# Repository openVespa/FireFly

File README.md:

# FireFly
The digital ignition controller, called the FireFly Mini, uses the stock Variable Reluctor (VR) pickup and is the typical retard only system. Also includes (2) K-type thermocouple inputs for Exhaust Gas Temperature (EGT) and Cylinder Head Temperature (CHT) monitoring. The goal is to provide a programmable ignition controller that dynamically adjusts based on EGT and CHT values.  A Windows program allows you to customize ignition curves over USB; log RPM, CHT, and EGT values; and flash the firmware. You can save maps, read the map that is loaded,etc. I've also created an basic android app that displays the RPM, CHT, and EGT values. In addition, the FF mini simulates the popular OBDII ELM327 interface. This allows my old Vespa to have an "OBD II ecu", allowing you to take advantage of the many ELM327 based apps available. My personal favorite is the Torque app.

The GUI was developed using Microsoft Visual C# 2010 and relies heavily on the Generic HID program and contains portions of the WFF GenericHID Communication Library which is (c)2011 Simon Inns - http://www.waitingforfriday.com 

The Eagle schematics and board files are provided, along with the BOM, and the Gerbers. The circuit card was designed to fit into a Polycase LP-11F enclosure.  The design uses an atmega16u2 and the source code was developed in Atmel Studio 6.1.  The USB stack is based on the LUFA USB Library.

http://www.fourwalledcubicle.com/LUFA.php

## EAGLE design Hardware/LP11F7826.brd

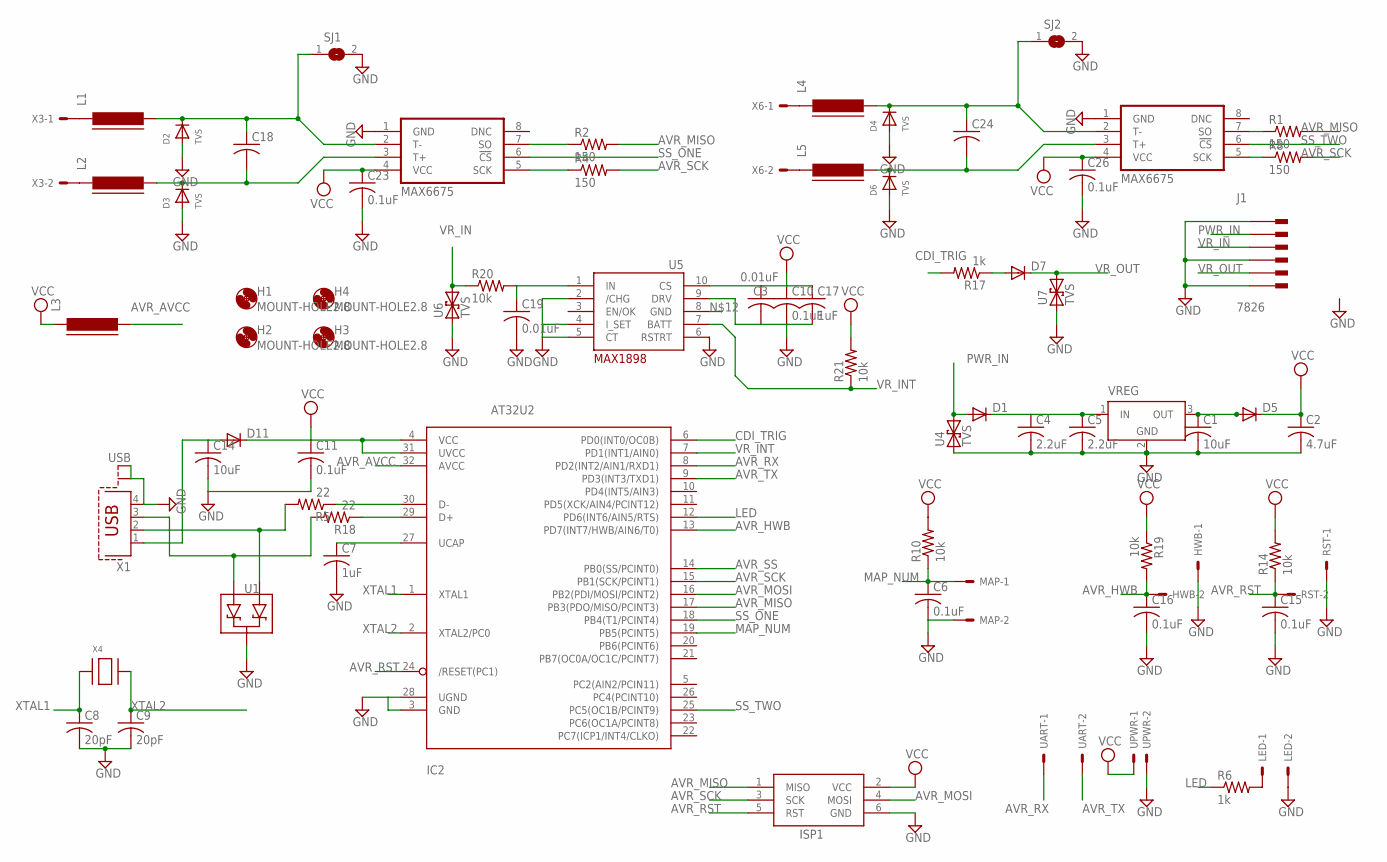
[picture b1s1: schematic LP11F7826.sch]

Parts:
C1: 10uF; C1206
C2: 4.7uF; C1210
C3, C19: 0.01uF; C0805
C4: 2.2uF; C1206
C5: 2.2uF; C1210
C6, C10, C11, C15, C16, C23, C26: 0.1uF; C0805
C7, C17: 1uF; C0805
C8, C9: 20pF; C0805
C14: 10uF; C0805
C18, C24: C-USC0805; C0805
D1, D5, D7, D11: CGRM4001-G; SOD-123_MINI-SMA
D2, D3, D4, D6: TVS; SOD-323F
H1, H2, H3, H4: MOUNT-HOLE2.8; 2,8
HWB: 87758-0216; MPN 87758-0216
IC1, IC3: MAX6675; SO-8
IC2: AT32U2; TQFP32-08
ISP1: AVRISP-6; AVRISP
J1: 7826; 7806HEADER
L1, L2, L3, L4, L5: FERRITE-0805; FB805
LED: 87758-0216; MPN 87758-0216
MAP: 87758-0216
R1, R2, R4, R8: 150; R0805
R5, R18: 22; R0805
R6, R17: 1k; R0805
R10, R14, R19, R20, R21: 10k; R0805
RST: 87758-0216; MPN 87758-0216
SJ1, SJ2: SJ
U1: MMBZ27VCLT1; SOT23-3
U4, U6, U7: TVS; SMA-DIODE
U5: MAX9924; UMAX10
UART: 87758-0216; MPN 87758-0216
UPWR: 87758-0216; MPN 87758-0216
VREG: LT1963EST-3.3; SOT223
X1: USB; PN61729-S
X3, X6: 22-23-2021; MPN 22-23-2021
X4: XTALNX5032; NX5032

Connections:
AVR_AVCC: IC2.32 (AVCC), L3.2
AVR_HWB: C16.1, HWB.2, IC2.13 (PD7(INT7/HWB/AIN6/T0)), R19.2
AVR_MISO: IC2.17 (PB3(PDO/MISO/PCINT3)), ISP1.1 (MISO), R1.2, R2.2
AVR_MOSI: IC2.16 (PB2(PDI/MOSI/PCINT2)), ISP1.4 (MOSI)
AVR_RST: C15.1, IC2.24 (/RESET(PC1)), ISP1.5 (RST), R14.1, RST.2
AVR_RX: IC2.8 (PD2(INT2/AIN1/RXD1)), UART.1
AVR_SCK: IC2.15 (PB1(SCK/PCINT1)), ISP1.3 (SCK), R4.2, R8.2
AVR_SS: IC2.14 (PB0(SS/PCINT0))
AVR_TX: IC2.9 (PD3(INT3/TXD1)), UART.2
CDI_TRIG: IC2.6 (PD0(INT0/OC0B)), R17.2
GND: C1.2, C2.2, C3.2, C4.2, C5.2, C6.2, C7.2, C8.2, C9.2, C10.2, C11.2, C14.2, C15.2, C16.2, C17.2, C19.2, C23.2, C26.2, D2.A, D3.A, D4.A, D6.A, HWB.1, IC1.1 (GND), IC2.3 (GND), IC2.28 (UGND), IC3.1 (GND), ISP1.6 (GND), J1.A1 (1), J1.A2 (1), J1.A5 (3), J1.A6 (3), J1.A11 (6), J1.A12 (6), LED.2, MAP.2, RST.1, SJ1.2, SJ2.2, U1.3 (C), U4.A (1), U5.2 (/CHG), U5.4 (I_SET), U5.5 (CT), U5.6 (RSTRT), U5.9 (DRV), U6.A (1), U7.A (1), UPWR.2, VREG.2 (GND), VREG.4 (GND), X1.4, X1.S1, X1.S2
LED: IC2.12 (PD6(INT6/AIN5/RTS)), R6.1
MAP_NUM: C6.1, IC2.19 (PB5(PCINT5)), MAP.1, R10.1
unnamed: C14.1, D11.A, X1.1
unnamed: C4.1, C5.1, D1.C, VREG.1 (IN)
unnamed: C18.1, D2.C, IC3.2 (T-), L1.2, SJ1.1
unnamed: C18.2, D3.C, IC3.3 (T+), L2.2
unnamed: C1.1, D5.A, VREG.3 (OUT)
unnamed: LED.1, R6.2
unnamed: C24.1, D4.C, IC1.2 (T-), L4.2, SJ2.1
unnamed: C24.2, D6.C, IC1.3 (T+), L5.2
unnamed: IC1.5 (SCK), R8.1
unnamed: IC2.30 (D-), R5.1
unnamed: L1.1, X3.1
unnamed: L2.1, X3.2
unnamed: IC3.5 (SCK), R4.1
unnamed: IC2.29 (D+), R18.1
unnamed: C7.1, IC2.27 (UCAP)
unnamed: IC3.7 (SO), R2.1
unnamed: IC1.7 (SO), R1.1
unnamed: L4.1, X6.1
unnamed: L5.1, X6.2
unnamed: R5.2, U1.1 (A1), X1.2
unnamed: R18.2, U1.2 (A2), X1.3
unnamed: D7.A, R17.1
unnamed: C19.1, R20.2, U5.1 (IN)
PWR_IN: D1.A, J1.A9 (5), J1.A10 (5), U4.C (2)
SS_ONE: IC2.18 (PB4(T1/PCINT4)), IC3.6 (!CS)
SS_TWO: IC1.6 (!CS), IC2.25 (PC5(OC1B/PCINT9))
VCC: C2.1, C3.1, C10.1, C11.1, C17.1, C23.1, C26.1, D5.C, D11.C, IC1.4 (VCC), IC2.4 (VCC), IC2.31 (UVCC), IC3.4 (VCC), ISP1.2 (VCC), L3.1, R10.2, R14.2, R19.1, R21.2, U5.10 (CS), UPWR.1
VR_IN: J1.A7 (4), J1.A8 (4), R20.1, U6.C (2)
VR_INT: IC2.7 (PD1(INT1/AIN0)), R21.1, U5.7 (BATT)
VR_OUT: D7.C, J1.A3 (2), J1.A4 (2), U7.C (2)
XTAL1: C8.1, IC2.1 (XTAL1), X4.P$1
XTAL2: C9.1, IC2.2 (XTAL2/PC0), X4.P$2

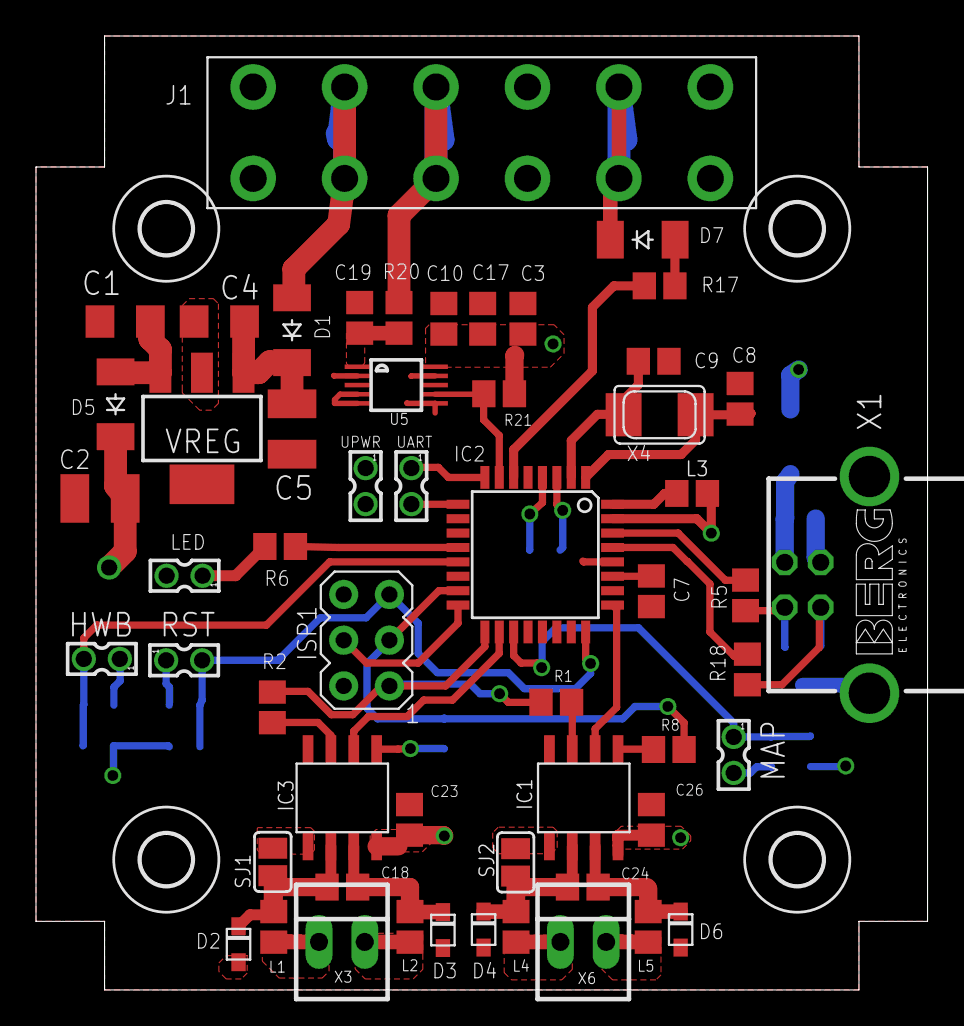
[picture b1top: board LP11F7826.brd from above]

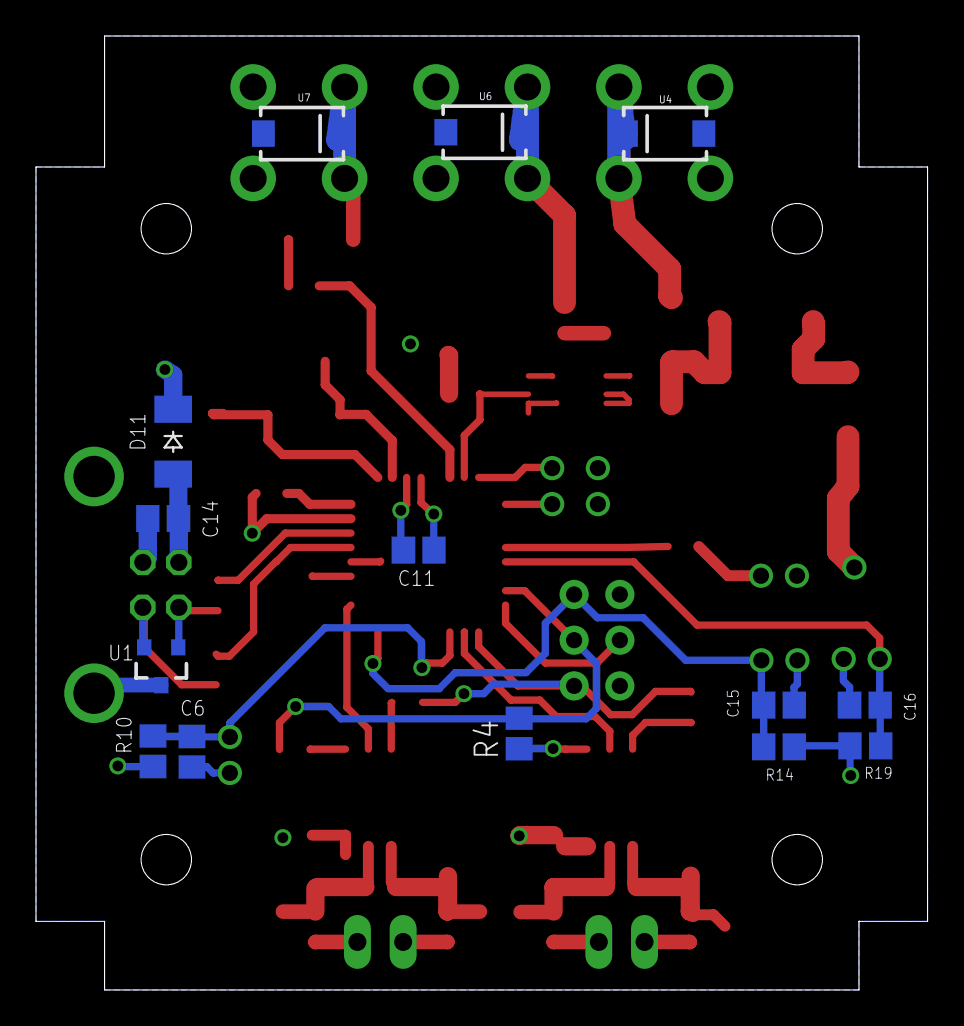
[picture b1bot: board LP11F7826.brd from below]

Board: 2 copper layers, 49.5 x 53.0 mm, 73 parts (14 on the bottom side), 44 nets.

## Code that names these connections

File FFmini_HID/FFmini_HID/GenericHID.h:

/*
             LUFA Library
     Copyright (C) Dean Camera, 2014.

  dean [at] fourwalledcubicle [dot] com
           www.lufa-lib.org
*/

/*
  Copyright 2014  Dean Camera (dean [at] fourwalledcubicle [dot] com)

  Permission to use, copy, modify, distribute, and sell this
  software and its documentation for any purpose is hereby granted
  without fee, provided that the above copyright notice appear in
  all copies and that both that the copyright notice and this
  permission notice and warranty disclaimer appear in supporting
  documentation, and that the name of the author not be used in
  advertising or publicity pertaining to distribution of the
  software without specific, written prior permission.

  The author disclaims all warranties with regard to this
  software, including all implied warranties of merchantability
  and fitness.  In no event shall the author be liable for any
  special, indirect or consequential damages or any damages
  whatsoever resulting from loss of use, data or profits, whether
  in an action of contract, negligence or other tortious action,
  arising out of or in connection with the use or performance of
  this software.
*/

/** \file
 *
 *  Header file for GenericHID.c.
 */

#ifndef _GENERICHID_H_
#define _GENERICHID_H_

	/* Includes: */
		#include <avr/pgmspace.h>
		#include <avr/io.h>
		#include <avr/wdt.h>
		#include <avr/power.h>
		#include <avr/interrupt.h>
		#include <string.h>
		#include <avr/eeprom.h>
		#include <util/delay.h>

		#include "Descriptors.h"
		#include "Config/AppConfig.h"

		//#include <LUFA/Drivers/Board/LEDs.h>
		#include <LUFA/Drivers/USB/USB.h>
		#include <LUFA/Platform/Platform.h>
		#include <LUFA/Drivers/Peripheral/SPI.h>
		#include <LUFA/Drivers/Peripheral/Serial.h>
		#include <LUFA/Drivers/Misc/RingBuffer.h>

		#include "EXT.h"
		#include "TIMERS.h"
		#include "AT_parser.h"
		#include "reset.h"

	/* Macros: */
		/** LED mask for the library LED driver, to indicate that the USB interface is not ready. */
		//#define LEDMASK_USB_NOTREADY      LEDS_LED1

		/** LED mask for the library LED driver, to indicate that the USB interface is enumerating. */
		//#define LEDMASK_USB_ENUMERATING  (LEDS_LED2 | LEDS_LED3)

		/** LED mask for the library LED driver, to indicate that the USB interface is ready. */
		//#define LEDMASK_USB_READY        (LEDS_LED2 | LEDS_LED4)

		/** LED mask for the library LED driver, to indicate that an error has occurred in the USB interface. */
		//#define LEDMASK_USB_ERROR        (LEDS_LED1 | LEDS_LED3)
// FF PULL
#ifndef IGN_TRIGGER
#define IGN_TRIGGER     PD0   // Ignition Trigger
#endif

#ifndef MAP_SW
#define MAP_SW	        PB5   // GREEN
#endif

#ifndef MAIN_LED
#define MAIN_LED		PD6   // GREEN
#endif

#ifndef MAXCHT
#define MAXCHT	        PB4   // MAX6675 CS
#endif

#ifndef MAXEGT
#define MAXEGT	        PC5   // MAX6675 CS
#endif

#define STACK_CANARY	0xC5
	/* Function Prototypes: */
		void SetupHardware(void);

		void EVENT_USB_Device_Connect(void);
		void EVENT_USB_Device_Disconnect(void);
		void EVENT_USB_Device_ConfigurationChanged(void);
		void EVENT_USB_Device_ControlRequest(void);
		void EVENT_USB_Device_StartOfFrame(void);

		bool CALLBACK_HID_Device_CreateHIDReport(USB_ClassInfo_HID_Device_t* const HIDInterfaceInfo,
		                                         uint8_t* const ReportID,
		                                         const uint8_t ReportType,
		                                         void* ReportData,
		                                         uint16_t* const ReportSize);
		void CALLBACK_HID_Device_ProcessHIDReport(USB_ClassInfo_HID_Device_t* const HIDInterfaceInfo,
		                                          const uint8_t ReportID,
		                                          const uint8_t ReportType,
		                                          const void* ReportData,
		                                          const uint16_t ReportSize);

#endif

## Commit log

2016-04-15 Added files via upload
2016-04-15 d
    s
2016-10-11 unzipping

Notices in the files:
parts and their libraries:
SparkFun-DiscreteSemi: Licensing: CC v3.0 Share-Alike You are welcome to use this library for commercial purposes.
